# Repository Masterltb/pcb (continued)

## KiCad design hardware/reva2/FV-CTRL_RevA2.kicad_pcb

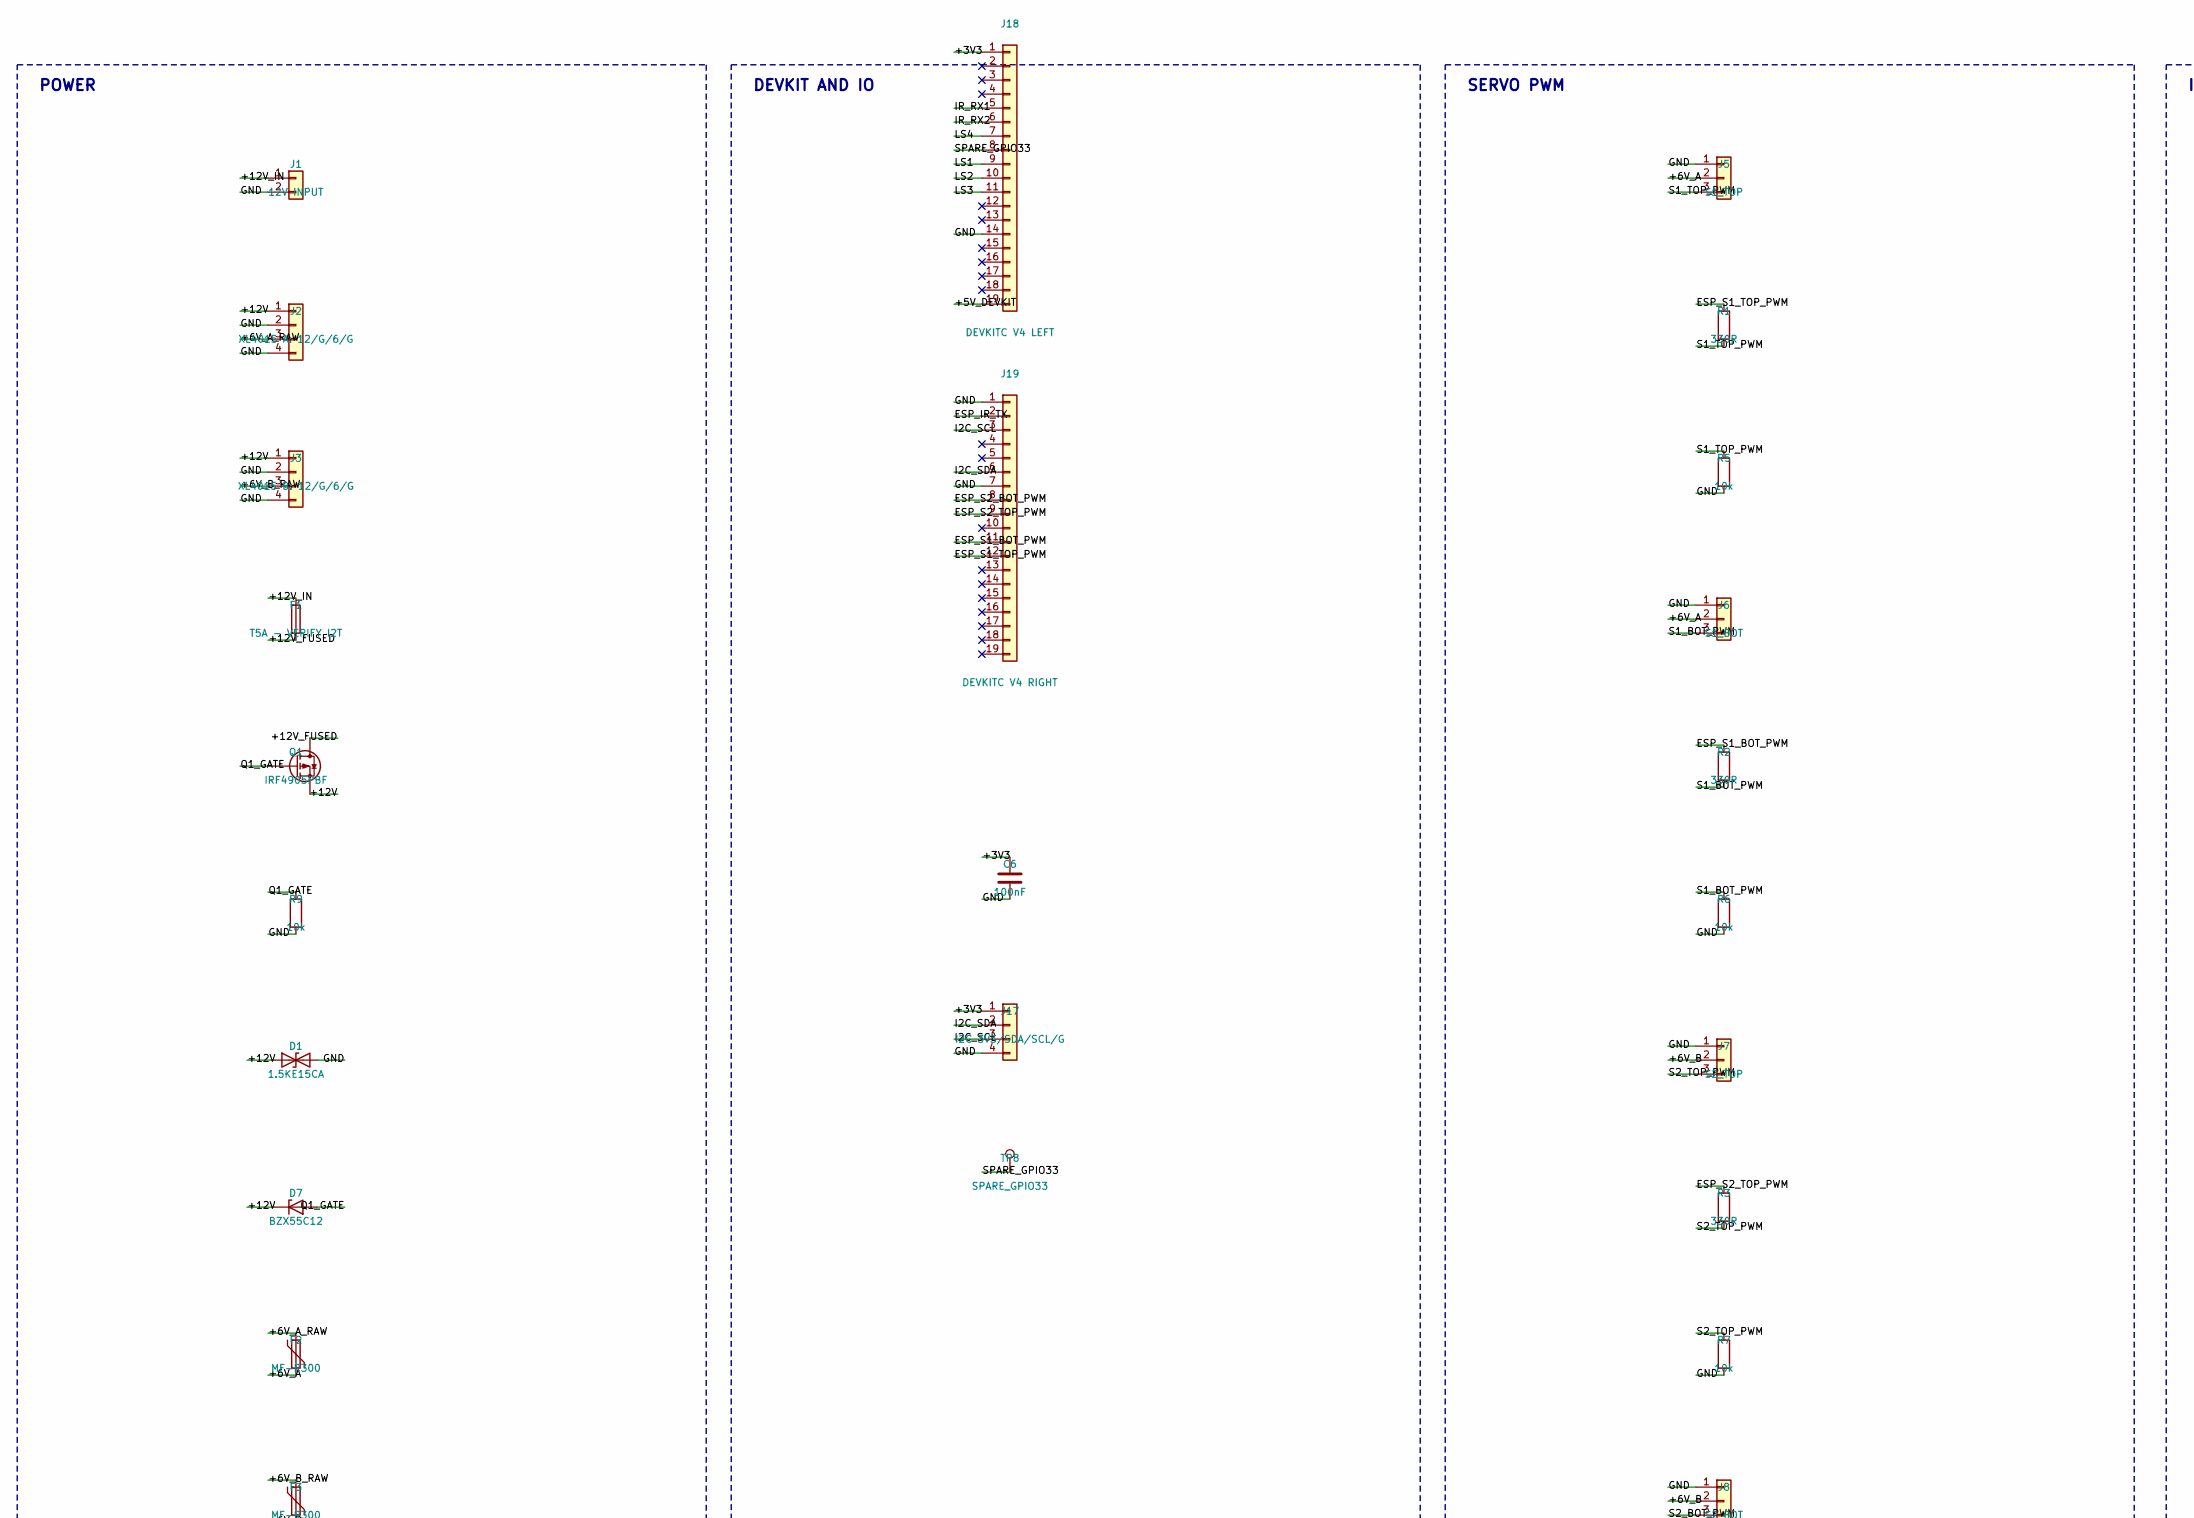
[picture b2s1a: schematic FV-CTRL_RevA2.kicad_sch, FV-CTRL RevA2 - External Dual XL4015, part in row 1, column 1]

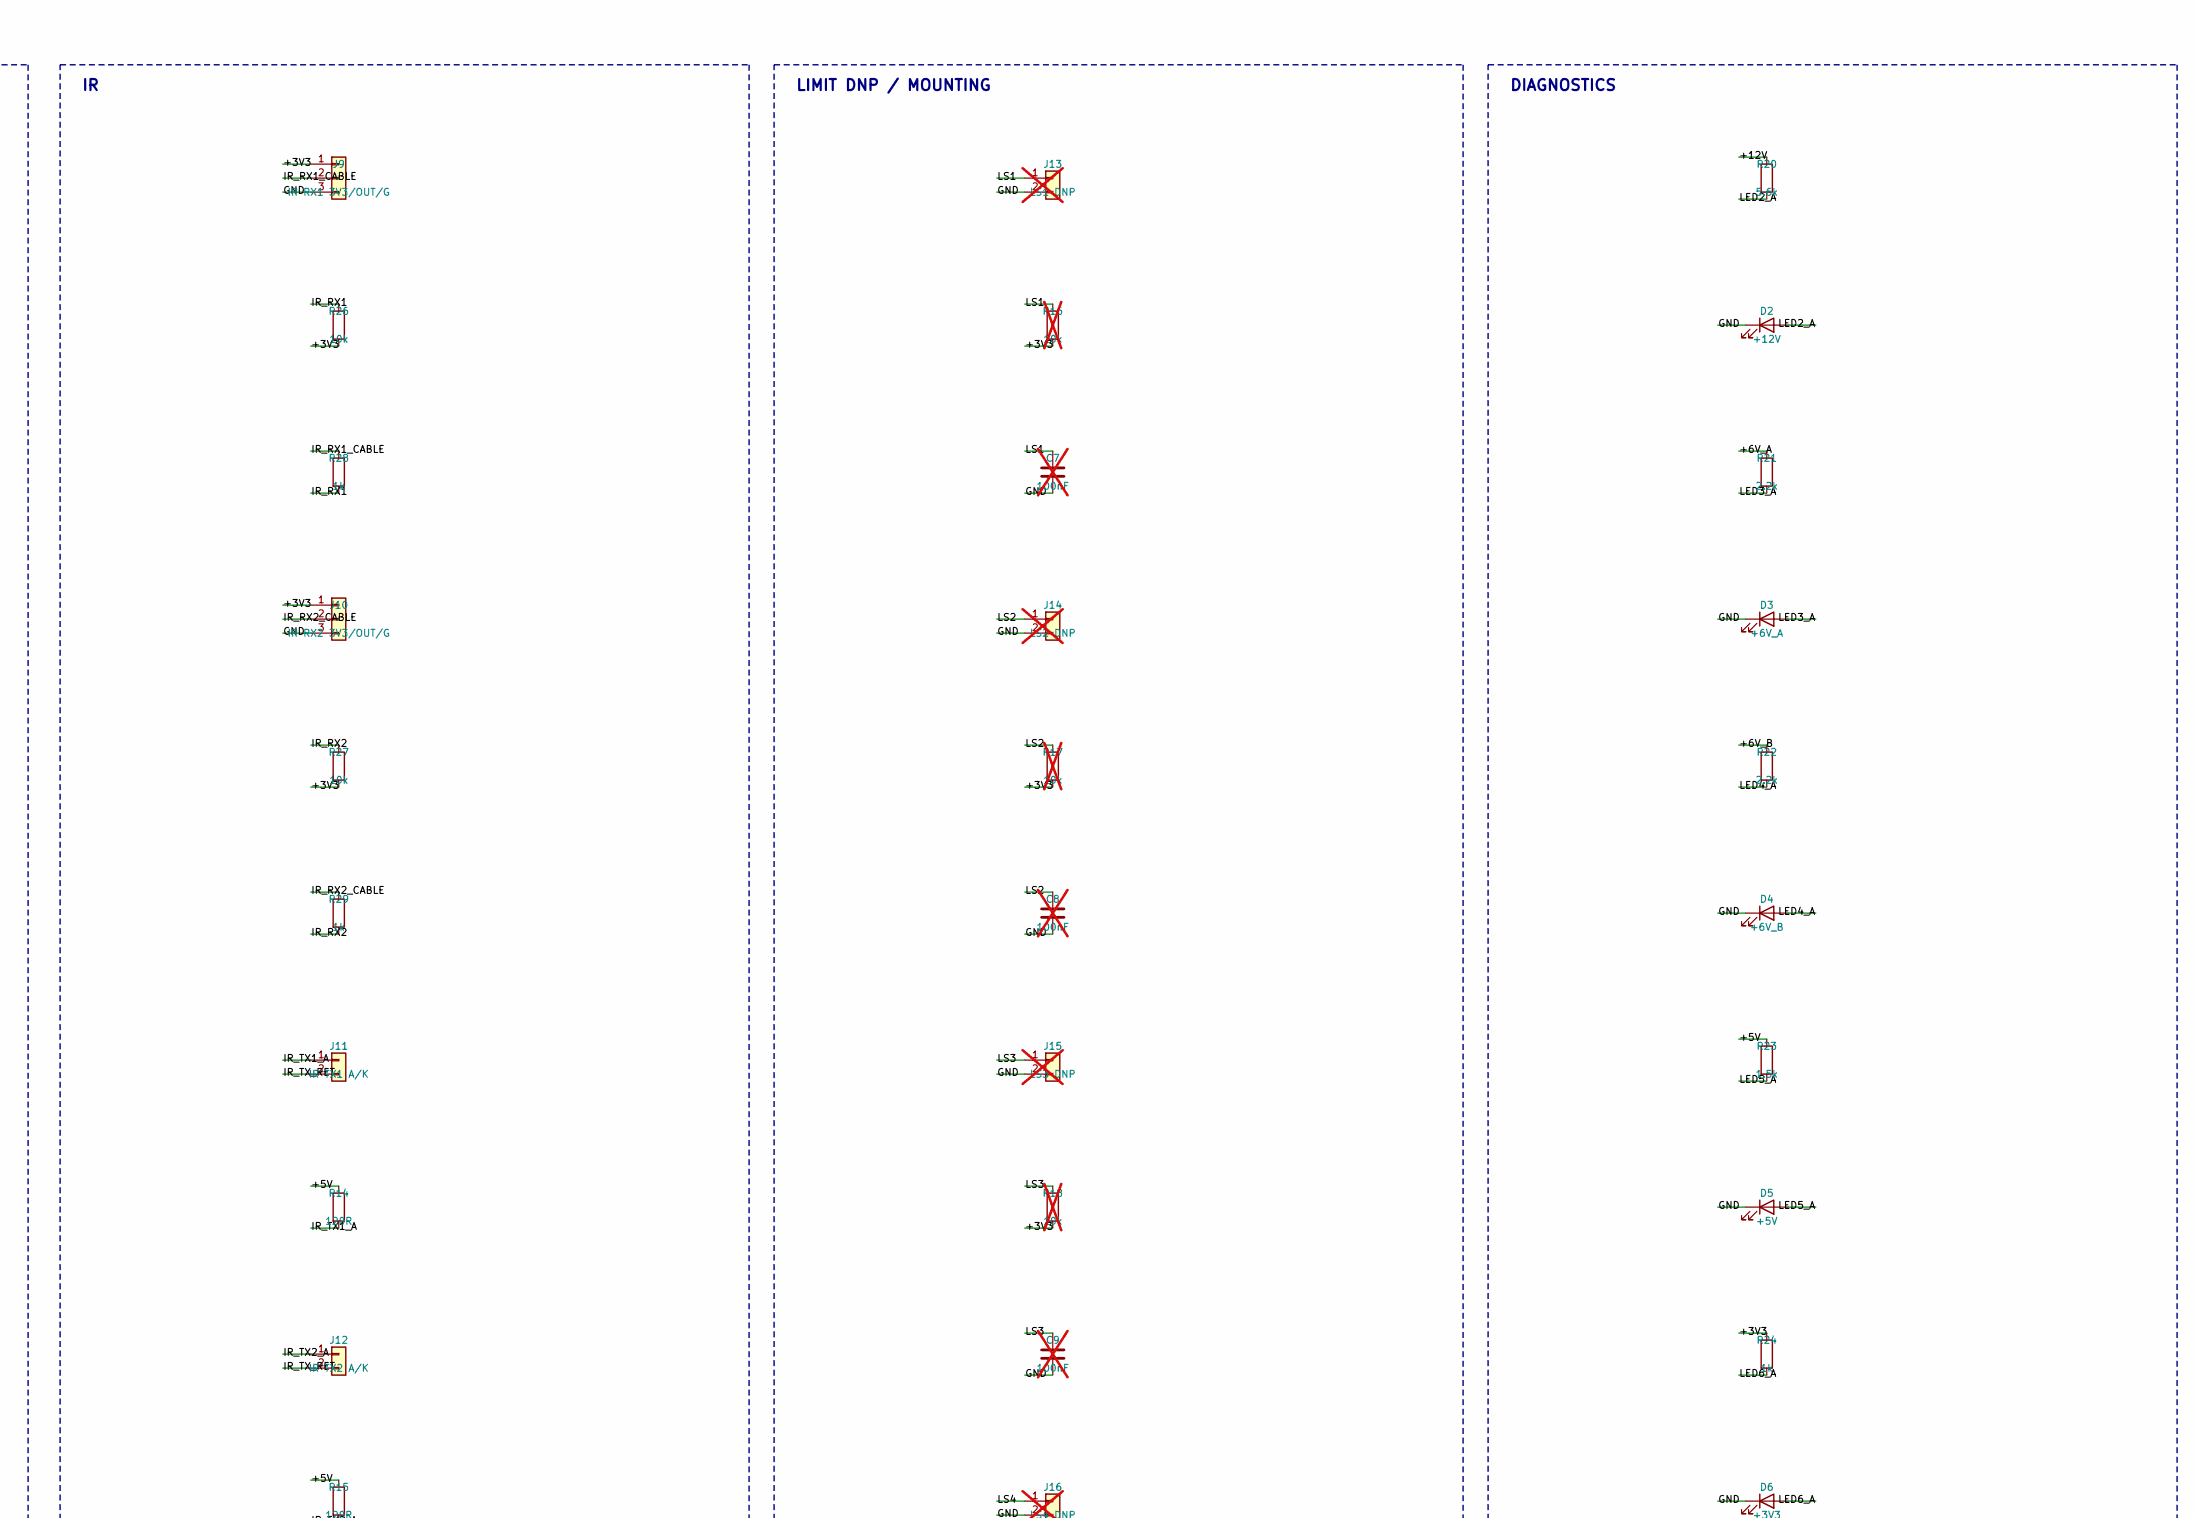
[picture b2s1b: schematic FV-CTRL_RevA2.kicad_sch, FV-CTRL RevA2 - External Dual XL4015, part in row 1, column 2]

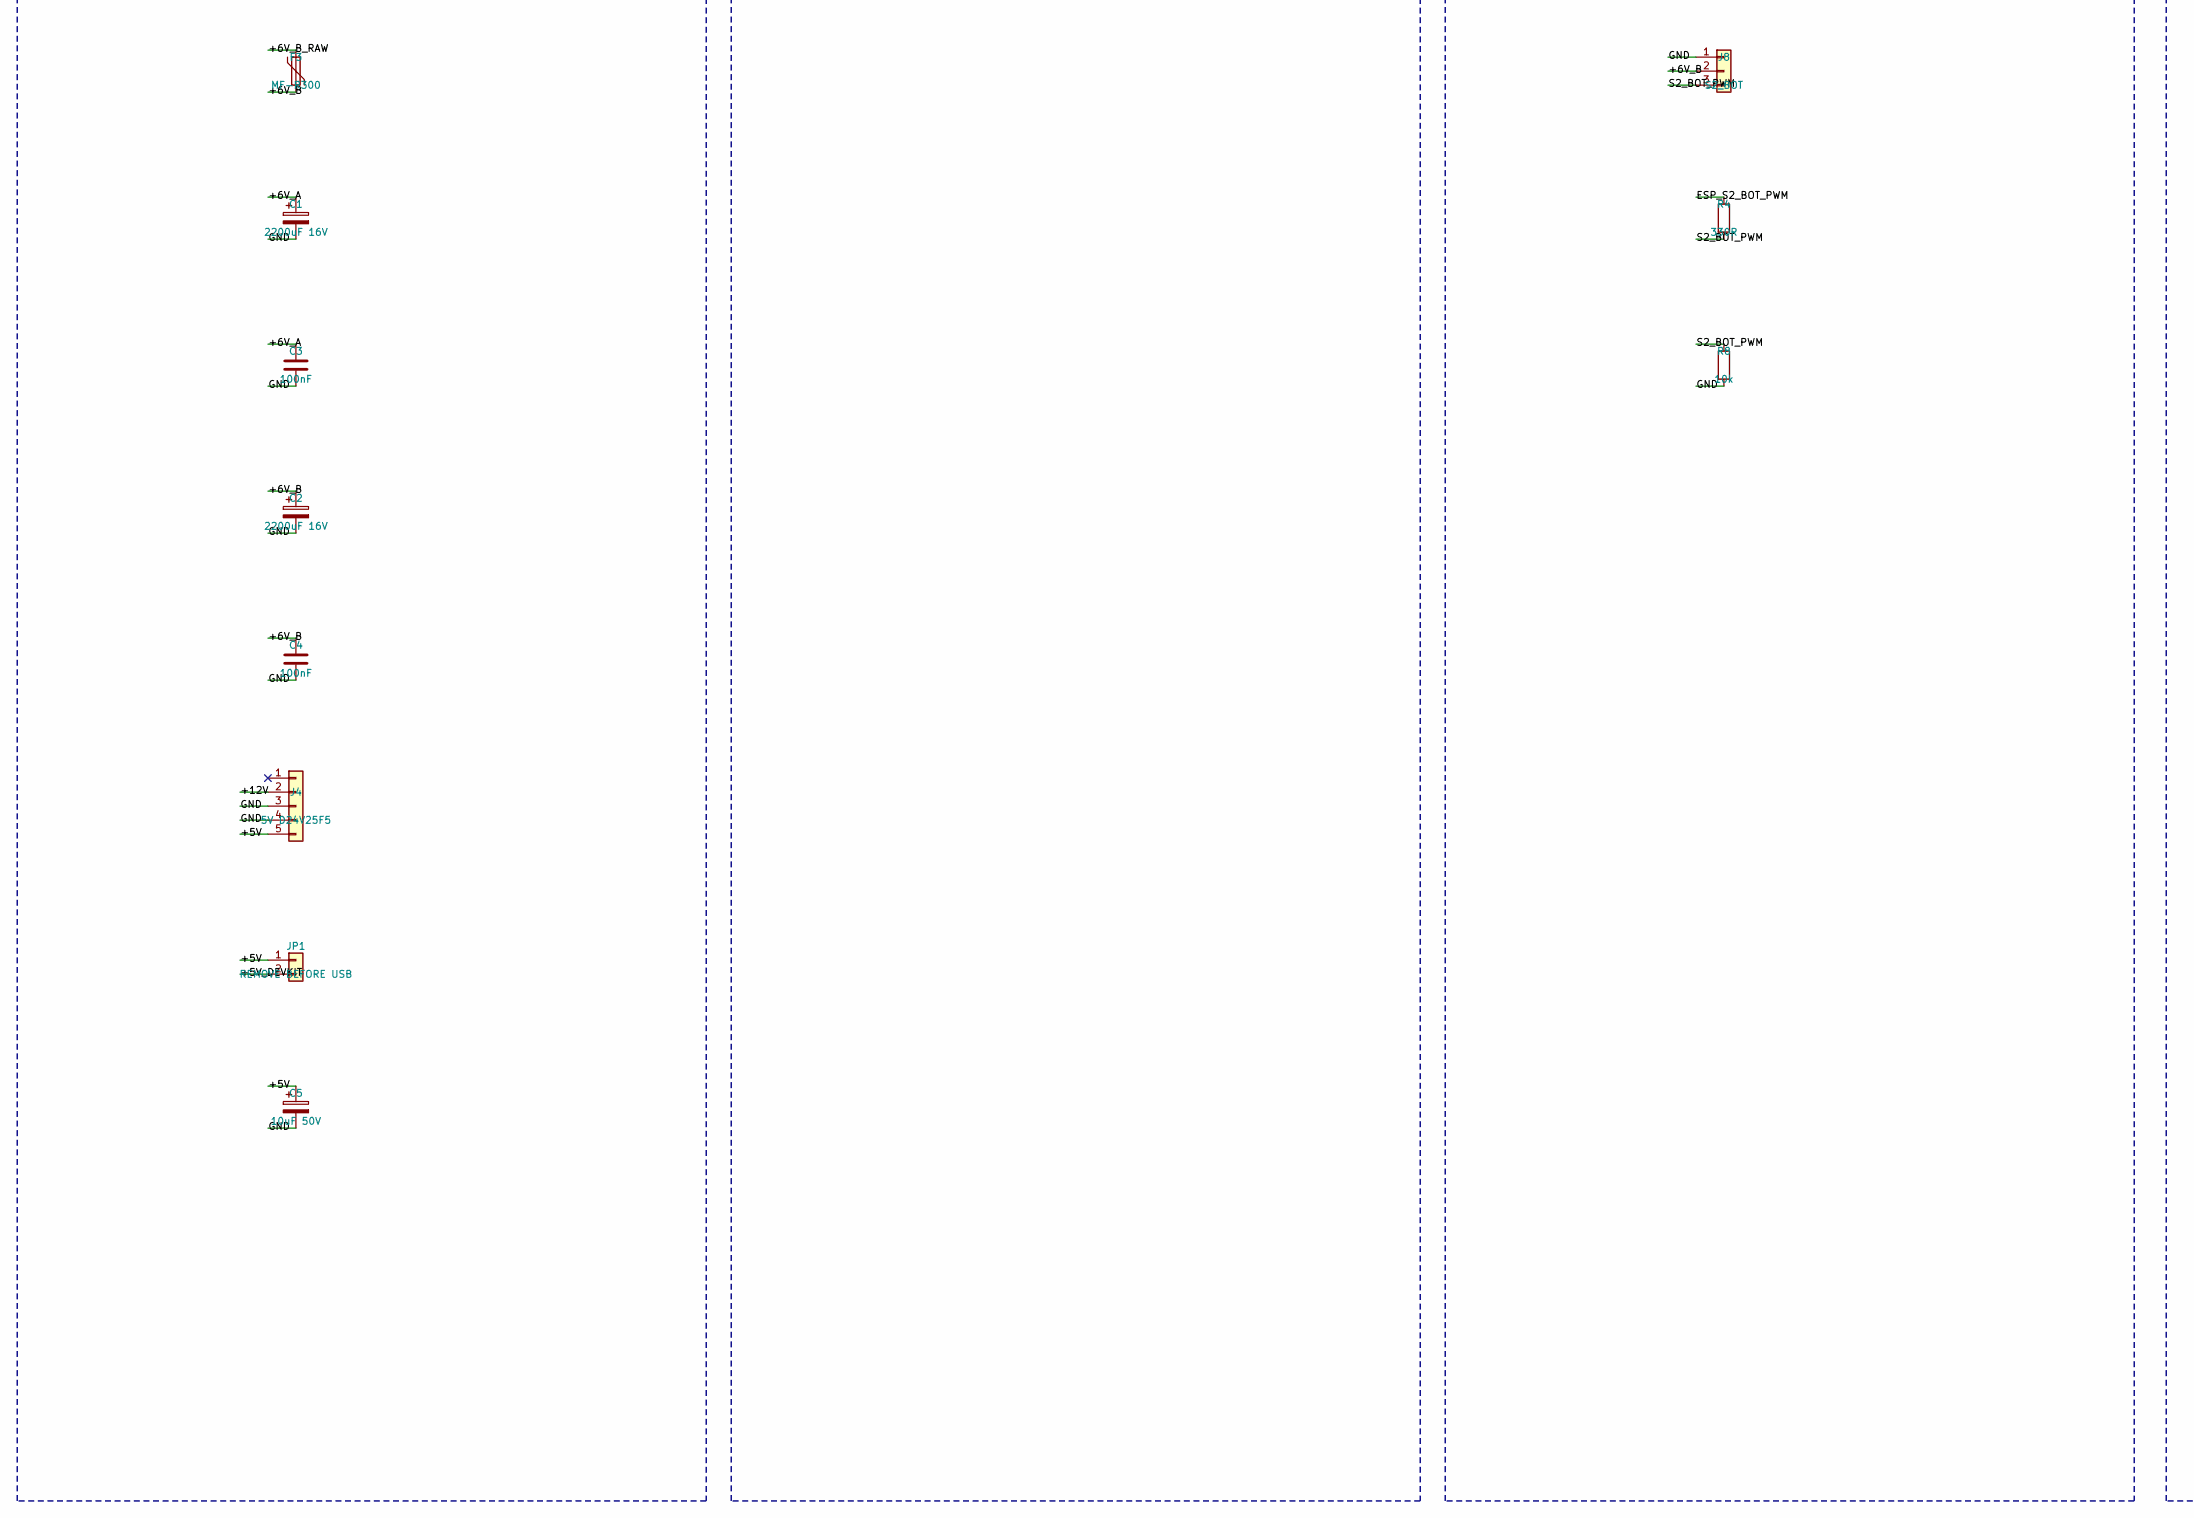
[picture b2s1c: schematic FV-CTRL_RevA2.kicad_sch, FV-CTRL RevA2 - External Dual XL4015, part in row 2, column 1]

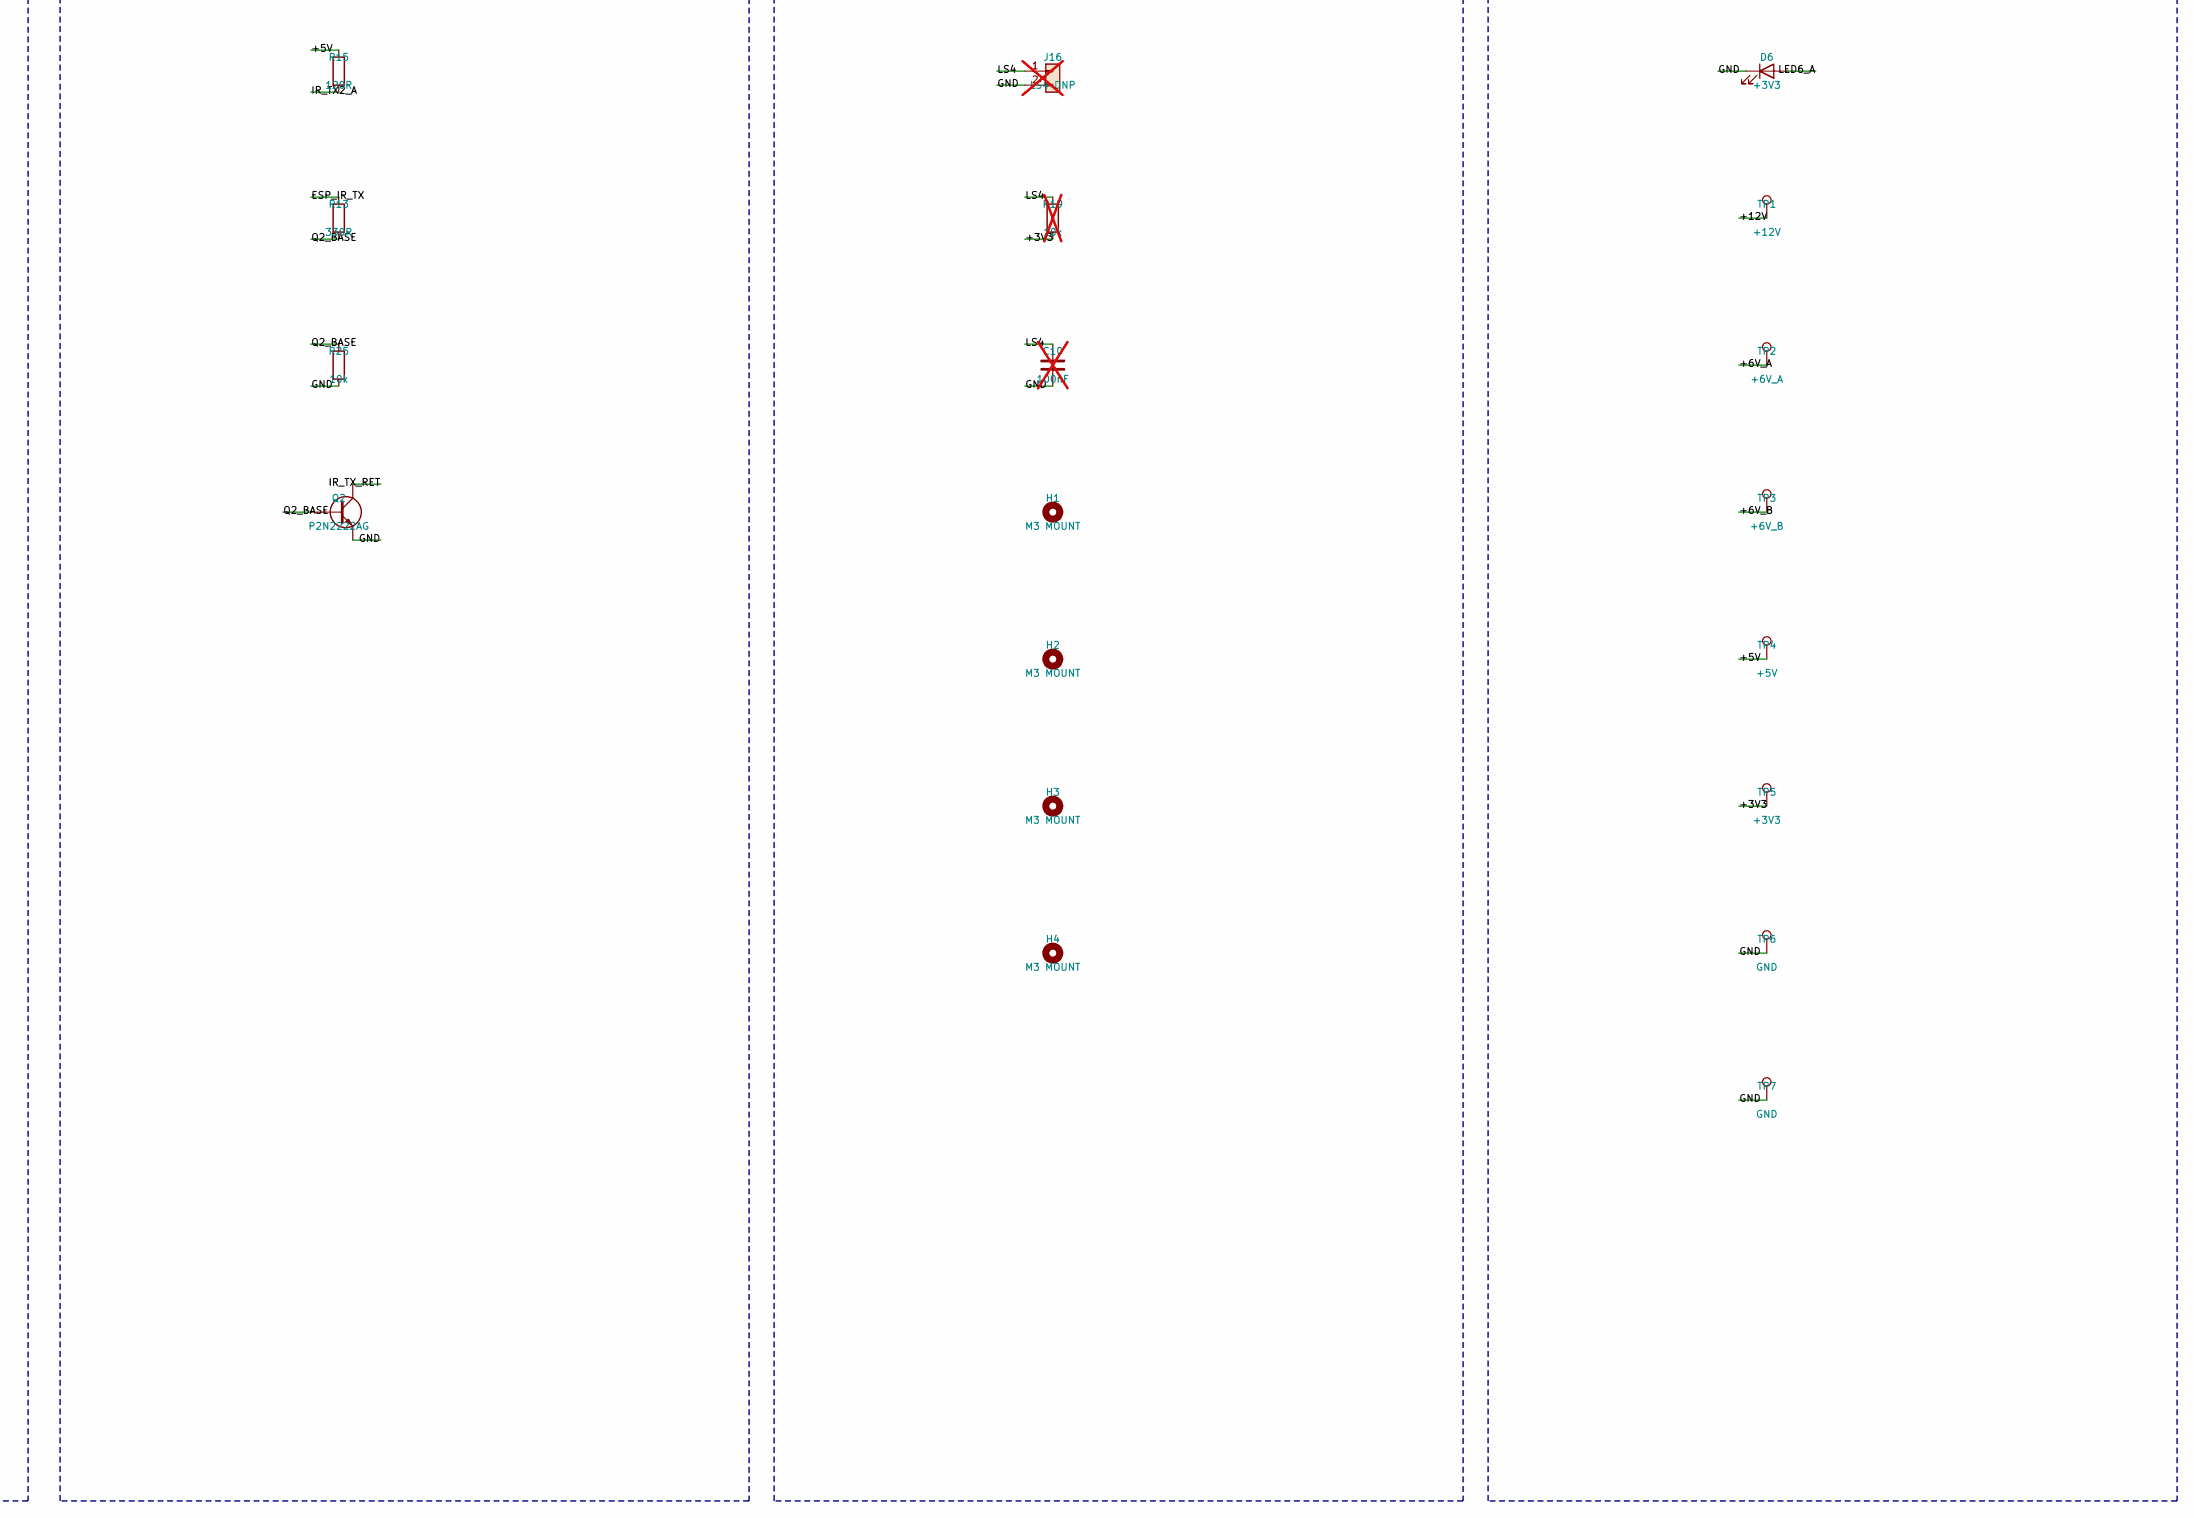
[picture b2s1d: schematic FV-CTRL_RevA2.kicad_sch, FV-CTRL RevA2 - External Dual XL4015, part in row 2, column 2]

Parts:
C1, C2: 2200uF 16V; CP_Radial_D12.5mm_P5.00mm
C3, C4, C6: 100nF; C_Disc_D5.0mm_W2.5mm_P5.00mm
C5: 10uF 50V; CP_Radial_D5.0mm_P2.00mm
C7, C8, C9, C10: 100nF; C_Disc_D5.0mm_W2.5mm_P5.00mm; not fitted
D1: 1.5KE15CA; D_DO-201AD_P15.24mm_Horizontal
D2: +12V; LED_D3.0mm
D3: +6V_A; LED_D3.0mm
D4: +6V_B; LED_D3.0mm
D5: +5V; LED_D3.0mm
D6: +3V3; LED_D3.0mm
D7: BZX55C12; D_DO-35_SOD27_P7.62mm_Horizontal
F1: T5A - VERIFY I2T; Fuseholder_Clip-5x20mm_Littelfuse_111_Inline_P20.00x5.00mm_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
F2, F3: MF-R300; MF_R300
H1, H2, H3, H4: M3 MOUNT; MountingHole_3.2mm_M3
J1: 12V INPUT; PhoenixContact_MSTBA_2,5_2-G-5,08_1x02_P5.08mm_Horizontal
J2: XL4015 A: 12/G/6/G; PhoenixContact_MSTBA_2,5_4-G-5,08_1x04_P5.08mm_Horizontal
J3: XL4015 B: 12/G/6/G; PhoenixContact_MSTBA_2,5_4-G-5,08_1x04_P5.08mm_Horizontal
J4: 5V D24V25F5; Pololu_D24V25F5
J5: S1_TOP; PinHeader_1x03_P2.54mm_Vertical
J6: S1_BOT; PinHeader_1x03_P2.54mm_Vertical
J7: S2_TOP; PinHeader_1x03_P2.54mm_Vertical
J8: S2_BOT; PinHeader_1x03_P2.54mm_Vertical
J9: IR RX1 3V3/OUT/G; JST_XH_B3B-XH-A_1x03_P2.50mm_Vertical
J10: IR RX2 3V3/OUT/G; JST_XH_B3B-XH-A_1x03_P2.50mm_Vertical
J11: IR TX1 A/K; JST_XH_B2B-XH-A_1x02_P2.50mm_Vertical
J12: IR TX2 A/K; JST_XH_B2B-XH-A_1x02_P2.50mm_Vertical
J13: LS1 DNP; JST_XH_B2B-XH-A_1x02_P2.50mm_Vertical; not fitted
J14: LS2 DNP; JST_XH_B2B-XH-A_1x02_P2.50mm_Vertical; not fitted
J15: LS3 DNP; JST_XH_B2B-XH-A_1x02_P2.50mm_Vertical; not fitted
J16: LS4 DNP; JST_XH_B2B-XH-A_1x02_P2.50mm_Vertical; not fitted
J17: I2C 3V3/SDA/SCL/G; PinHeader_1x04_P2.54mm_Vertical
J18: DEVKITC V4 LEFT; PinSocket_1x19_P2.54mm_Vertical
J19: DEVKITC V4 RIGHT; PinSocket_1x19_P2.54mm_Vertical
JP1: REMOVE BEFORE USB; PinHeader_1x02_P2.54mm_Vertical
Q1: IRF4905PBF; PMOS_GDS
Q2: P2N2222AG; NPN_CBE
R1, R2, R3, R4, R13: 330R; R_Axial_DIN0207_L6.3mm_D2.5mm_P7.62mm_Horizontal
R5, R6, R7, R8, R9, R25, R26, R27: 10k; R_Axial_DIN0207_L6.3mm_D2.5mm_P7.62mm_Horizontal
R14, R15: 120R; R_Axial_DIN0207_L6.3mm_D2.5mm_P7.62mm_Horizontal
R16, R17, R18, R19: 10k; R_Axial_DIN0207_L6.3mm_D2.5mm_P7.62mm_Horizontal; not fitted
R20: 5.6k; R_Axial_DIN0207_L6.3mm_D2.5mm_P7.62mm_Horizontal
R21, R22: 2.2k; R_Axial_DIN0207_L6.3mm_D2.5mm_P7.62mm_Horizontal
R23: 1.5k; R_Axial_DIN0207_L6.3mm_D2.5mm_P7.62mm_Horizontal
R24, R28, R29: 1k; R_Axial_DIN0207_L6.3mm_D2.5mm_P7.62mm_Horizontal
TP1: +12V; Keystone_5000_Carrier_D3
TP2: +6V_A; Keystone_5000_Carrier_D3
TP3: +6V_B; Keystone_5000_Carrier_D3
TP4: +5V; Keystone_5000_Carrier_D3
TP5: +3V3; Keystone_5000_Carrier_D3
TP6, TP7: GND; Keystone_5000_Carrier_D3
TP8: SPARE_GPIO33; Keystone_5000_Carrier_D3

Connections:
/+3V3: C6.1, J9.1, J10.1, J17.1, J18.1, R16.2, R17.2, R18.2, R19.2, R24.1, R26.2, R27.2, TP5.1
/+5V: C5.1, J4.5, JP1.1, R14.1, R15.1, R23.1, TP4.1
/+5V_DEVKIT: J18.19, JP1.2
/+6V_A: C1.1, C3.1, F2.2, J5.2, J6.2, R21.1, TP2.1
/+6V_A_RAW: F2.1, J2.3
/+6V_B: C2.1, C4.1, F3.2, J7.2, J8.2, R22.1, TP3.1
/+6V_B_RAW: F3.1, J3.3
/+12V: D1.1 (A1), D7.1 (K), J2.1, J3.1, J4.2, Q1.S, R20.1, TP1.1
/+12V_FUSED: F1.2, Q1.D
/+12V_IN: F1.1, J1.1
/ESP_IR_TX: J19.2, R13.1
/ESP_S1_BOT_PWM: J19.11, R2.1
/ESP_S1_TOP_PWM: J19.12, R1.1
/ESP_S2_BOT_PWM: J19.8, R4.1
/ESP_S2_TOP_PWM: J19.9, R3.1
/GND: C1.2, C2.2, C3.2, C4.2, C5.2, C6.2, C7.2, C8.2, C9.2, C10.2, D1.2 (A2), D2.1 (K), D3.1 (K), D4.1 (K), D5.1 (K), D6.1 (K), J1.2, J2.2, J2.4, J3.2, J3.4, J4.3, J4.4, J5.1, J6.1, J7.1, J8.1, J9.3, J10.3, J13.2, J14.2, J15.2, J16.2, J17.4, J18.14, J19.1, J19.7, Q2.E, R5.2, R6.2, R7.2, R8.2, R9.2, R25.2, TP6.1, TP7.1
/I2C_SCL: J17.3, J19.3
/I2C_SDA: J17.2, J19.6
/IR_RX1: J18.5, R26.1, R28.2
/IR_RX1_CABLE: J9.2, R28.1
/IR_RX2: J18.6, R27.1, R29.2
/IR_RX2_CABLE: J10.2, R29.1
/IR_TX1_A: J11.1, R14.2
/IR_TX2_A: J12.1, R15.2
/IR_TX_RET: J11.2, J12.2, Q2.C
/LED2_A: D2.2 (A), R20.2
/LED3_A: D3.2 (A), R21.2
/LED4_A: D4.2 (A), R22.2
/LED5_A: D5.2 (A), R23.2
/LED6_A: D6.2 (A), R24.2
/LS1: C7.1, J13.1, J18.9, R16.1
/LS2: C8.1, J14.1, J18.10, R17.1
/LS3: C9.1, J15.1, J18.11, R18.1
/LS4: C10.1, J16.1, J18.7, R19.1
/Q1_GATE: D7.2 (A), Q1.G, R9.1
/Q2_BASE: Q2.B, R13.2, R25.1
/S1_BOT_PWM: J6.3, R2.2, R6.1
/S1_TOP_PWM: J5.3, R1.2, R5.1
/S2_BOT_PWM: J8.3, R4.2, R8.1
/S2_TOP_PWM: J7.3, R3.2, R7.1
/SPARE_GPIO33: J18.8, TP8.1

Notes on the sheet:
POWER
DEVKIT AND IO
SERVO PWM
LIMIT DNP / MOUNTING
DIAGNOSTICS

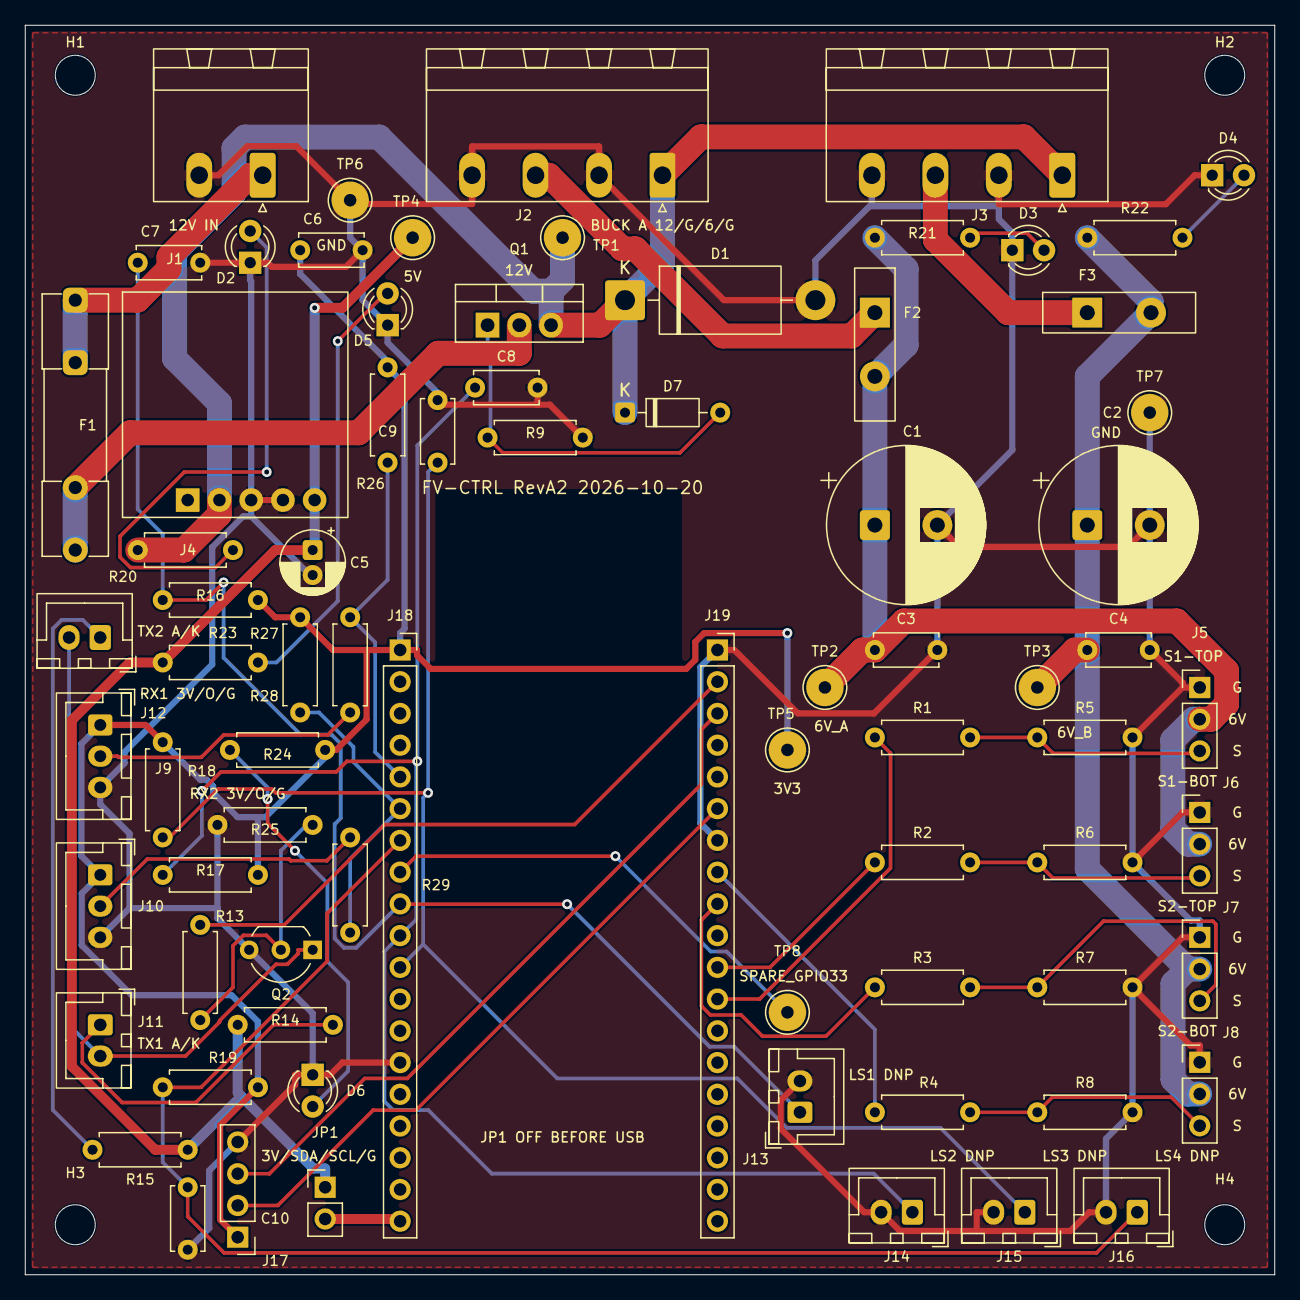
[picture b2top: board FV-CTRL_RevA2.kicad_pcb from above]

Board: 2 copper layers, 100.0 x 100.0 mm, 80 parts (0 on the bottom side), 41 nets.

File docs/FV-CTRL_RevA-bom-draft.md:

# BOM Nháp FV-CTRL Rev A (Engineering Draft)

| Ref | Giá trị / Mô tả | Thư viện | Footprint | DNP | MPN / Ghi chú |
|---|---|---|---|---|---|
| J1 | 12V_IN | `Connector_Generic:Conn_01x02` | TerminalBlock_Phoenix:TerminalBlock_Phoenix_MKDS-1,5-2-5.08_1x02_P5.08mm_Horizontal | No | Pluggable 2-pin 5.0mm |
| F1 | 5A 250V | `Device:Fuse` | Fuse:Fuseholder_Clip-5x20mm_Littelfuse_111_Inline_P20.00x5.00mm_D1.05mm_Horizontal | No | 5x20mm 5A cartridge |
| Q1 | IRF9540N | `Device:Q_PMOS` | Package_TO_SOT_THT:TO-220-3_Vertical | No | IRF9540NPBF |
| R9 | 10k | `Device:R` | Resistor_THT:R_Axial_DIN0207_L6.3mm_D2.5mm_P7.62mm_Horizontal | No | 10k 1/4W 5% |
| D1 | 1.5KE15CA | `Device:D_TVS` | Diode_THT:D_DO-201_P12.70mm_Horizontal | No | 1.5KE15CA |
| J2 | XH-M401 (6.0V 8A) | `Connector_Generic:Conn_01x04` | fv_modules:Converter_DCDC_XH-M401_8A | No | XH-M401 (XL4016E1 8A 200W) |
| J3 | AUX_BUCK (DNP) | `Connector_Generic:Conn_01x04` | Connector_PinHeader_2.54mm:PinHeader_1x04_P2.54mm_Vertical | DNP | Auxiliary 4-pin Header |
| J4 | MP1584EN (5V Logic) | `Connector_Generic:Conn_01x04` | fv_modules:Converter_DCDC_MP1584EN | No | MP1584EN Mini 3A Buck |
| F2 | PTC 3A | `Device:Polyfuse` | Fuse:Fuse_Bourns_MF-RG300 | No | Bourns MF-R300 |
| C1 | 1000-2200uF 16V | `Device:C_Polarized` | Capacitor_THT:CP_Radial_D12.5mm_P5.00mm | No | 1000uF 16V Radial |
| C3 | 100nF | `Device:C` | Capacitor_THT:C_Disc_D5.0mm_W2.5mm_P5.00mm | No | 100nF 50V Ceramic |
| J5 | S1_TOP | `Connector_Generic:Conn_01x03` | Connector_PinHeader_2.54mm:PinHeader_1x03_P2.54mm_Vertical | No | 3-pin Header |
| J6 | S1_BOT | `Connector_Generic:Conn_01x03` | Connector_PinHeader_2.54mm:PinHeader_1x03_P2.54mm_Vertical | No | 3-pin Header |
| F3 | PTC 3A | `Device:Polyfuse` | Fuse:Fuse_Bourns_MF-RG300 | No | Bourns MF-R300 |
| C2 | 1000-2200uF 16V | `Device:C_Polarized` | Capacitor_THT:CP_Radial_D12.5mm_P5.00mm | No | 1000uF 16V Radial |
| C4 | 100nF | `Device:C` | Capacitor_THT:C_Disc_D5.0mm_W2.5mm_P5.00mm | No | 100nF 50V Ceramic |
| J7 | S2_TOP | `Connector_Generic:Conn_01x03` | Connector_PinHeader_2.54mm:PinHeader_1x03_P2.54mm_Vertical | No | 3-pin Header |
| J8 | S2_BOT | `Connector_Generic:Conn_01x03` | Connector_PinHeader_2.54mm:PinHeader_1x03_P2.54mm_Vertical | No | 3-pin Header |
| J18 | ESP32_Left (Pins 1-19) | `Connector_Generic:Conn_01x19` | Connector_PinSocket_2.54mm:PinSocket_1x19_P2.54mm_Vertical | No | 19-pin Female Header 2.54mm |
| J19 | ESP32_Right (Pins 20-38) | `Connector_Generic:Conn_01x19` | Connector_PinSocket_2.54mm:PinSocket_1x19_P2.54mm_Vertical | No | 19-pin Female Header 2.54mm |
| R1 | 330R | `Device:R` | Resistor_THT:R_Axial_DIN0207_L6.3mm_D2.5mm_P7.62mm_Horizontal | No | 330R 1/4W 5% |
| R5 | 10k | `Device:R` | Resistor_THT:R_Axial_DIN0207_L6.3mm_D2.5mm_P7.62mm_Horizontal | No | 10k 1/4W 5% |
| R2 | 330R | `Device:R` | Resistor_THT:R_Axial_DIN0207_L6.3mm_D2.5mm_P7.62mm_Horizontal | No | 330R 1/4W 5% |
| R6 | 10k | `Device:R` | Resistor_THT:R_Axial_DIN0207_L6.3mm_D2.5mm_P7.62mm_Horizontal | No | 10k 1/4W 5% |
| R3 | 330R | `Device:R` | Resistor_THT:R_Axial_DIN0207_L6.3mm_D2.5mm_P7.62mm_Horizontal | No | 330R 1/4W 5% |
| R7 | 10k | `Device:R` | Resistor_THT:R_Axial_DIN0207_L6.3mm_D2.5mm_P7.62mm_Horizontal | No | 10k 1/4W 5% |
| R4 | 330R | `Device:R` | Resistor_THT:R_Axial_DIN0207_L6.3mm_D2.5mm_P7.62mm_Horizontal | No | 330R 1/4W 5% |
| R8 | 10k | `Device:R` | Resistor_THT:R_Axial_DIN0207_L6.3mm_D2.5mm_P7.62mm_Horizontal | No | 10k 1/4W 5% |
| R13 | 1k | `Device:R` | Resistor_THT:R_Axial_DIN0207_L6.3mm_D2.5mm_P7.62mm_Horizontal | No | 1k 1/4W 5% |
| Q2 | S8050 | `Device:Q_NPN` | Package_TO_SOT_THT:TO-92_Inline | No | S8050 |
| R14 | 120R | `Device:R` | Resistor_THT:R_Axial_DIN0207_L6.3mm_D2.5mm_P7.62mm_Horizontal | No | 120R 1/2W 5% |
| J11 | IR_TX1 (Col 1) | `Connector_Generic:Conn_01x02` | Connector_JST:JST_XH_B2B-XH-A_1x02_P2.50mm_Vertical | No | JST-XH 2-pin |
| R15 | 120R | `Device:R` | Resistor_THT:R_Axial_DIN0207_L6.3mm_D2.5mm_P7.62mm_Horizontal | No | 120R 1/2W 5% |
| J12 | IR_TX2 (Col 2) | `Connector_Generic:Conn_01x02` | Connector_JST:JST_XH_B2B-XH-A_1x02_P2.50mm_Vertical | No | JST-XH 2-pin |
| J9 | IR_RX1 | `Connector_Generic:Conn_01x03` | Connector_JST:JST_XH_B3B-XH-A_1x03_P2.50mm_Vertical | No | JST-XH 3-pin |
| J10 | IR_RX2 | `Connector_Generic:Conn_01x03` | Connector_JST:JST_XH_B3B-XH-A_1x03_P2.50mm_Vertical | No | JST-XH 3-pin |
| J13 | LS1 (DNP) | `Connector_Generic:Conn_01x02` | Connector_JST:JST_XH_B2B-XH-A_1x02_P2.50mm_Vertical | DNP | JST-XH 2-pin |
| R16 | 10k (DNP) | `Device:R` | Resistor_THT:R_Axial_DIN0207_L6.3mm_D2.5mm_P7.62mm_Horizontal | DNP | 10k 1/4W 5% |
| C7 | 100nF (DNP) | `Device:C` | Capacitor_THT:C_Disc_D5.0mm_W2.5mm_P5.00mm | DNP | 100nF 50V Ceramic |
| J14 | LS2 (DNP) | `Connector_Generic:Conn_01x02` | Connector_JST:JST_XH_B2B-XH-A_1x02_P2.50mm_Vertical | DNP | JST-XH 2-pin |
| R17 | 10k (DNP) | `Device:R` | Resistor_THT:R_Axial_DIN0207_L6.3mm_D2.5mm_P7.62mm_Horizontal | DNP | 10k 1/4W 5% |
| C8 | 100nF (DNP) | `Device:C` | Capacitor_THT:C_Disc_D5.0mm_W2.5mm_P5.00mm | DNP | 100nF 50V Ceramic |
| J15 | LS3 (DNP) | `Connector_Generic:Conn_01x02` | Connector_JST:JST_XH_B2B-XH-A_1x02_P2.50mm_Vertical | DNP | JST-XH 2-pin |
| R18 | 10k (DNP) | `Device:R` | Resistor_THT:R_Axial_DIN0207_L6.3mm_D2.5mm_P7.62mm_Horizontal | DNP | 10k 1/4W 5% |
| C9 | 100nF (DNP) | `Device:C` | Capacitor_THT:C_Disc_D5.0mm_W2.5mm_P5.00mm | DNP | 100nF 50V Ceramic |
| J16 | LS4 (DNP) | `Connector_Generic:Conn_01x02` | Connector_JST:JST_XH_B2B-XH-A_1x02_P2.50mm_Vertical | DNP | JST-XH 2-pin |
| R19 | 10k (DNP) | `Device:R` | Resistor_THT:R_Axial_DIN0207_L6.3mm_D2.5mm_P7.62mm_Horizontal | DNP | 10k 1/4W 5% |
| C10 | 100nF (DNP) | `Device:C` | Capacitor_THT:C_Disc_D5.0mm_W2.5mm_P5.00mm | DNP | 100nF 50V Ceramic |
| C5 | 10uF 16V | `Device:C_Polarized` | Capacitor_THT:C_Disc_D5.0mm_W2.5mm_P5.00mm | No | 10uF 16V Radial |
| C6 | 100nF | `Device:C` | Capacitor_THT:C_Disc_D5.0mm_W2.5mm_P5.00mm | No | 100nF 50V Ceramic |
| R20 | 5.6k | `Device:R` | Resistor_THT:R_Axial_DIN0207_L6.3mm_D2.5mm_P7.62mm_Horizontal | No | 5.6k 1/4W 5% |
| D2 | LED_+12V | `Device:LED` | LED_THT:LED_D3.0mm | No | 3mm Green LED |
| R21 | 2.2k | `Device:R` | Resistor_THT:R_Axial_DIN0207_L6.3mm_D2.5mm_P7.62mm_Horizontal | No | 2.2k 1/4W 5% |
| D3 | LED_+6V_A | `Device:LED` | LED_THT:LED_D3.0mm | No | 3mm Green LED |
| R22 | 2.2k | `Device:R` | Resistor_THT:R_Axial_DIN0207_L6.3mm_D2.5mm_P7.62mm_Horizontal | No | 2.2k 1/4W 5% |
| D4 | LED_+6V_B | `Device:LED` | LED_THT:LED_D3.0mm | No | 3mm Green LED |
| R23 | 1.5k | `Device:R` | Resistor_THT:R_Axial_DIN0207_L6.3mm_D2.5mm_P7.62mm_Horizontal | No | 1.5k 1/4W 5% |
| D5 | LED_+5V | `Device:LED` | LED_THT:LED_D3.0mm | No | 3mm Green LED |
| R24 | 1.0k | `Device:R` | Resistor_THT:R_Axial_DIN0207_L6.3mm_D2.5mm_P7.62mm_Horizontal | No | 1.0k 1/4W 5% |
| D6 | LED_+3V3 | `Device:LED` | LED_THT:LED_D3.0mm | No | 3mm Green LED |
| TP1 | TP_+12V | `Connector:TestPoint` | TestPoint:TestPoint_Pad_D2.0mm | No | Test Point Loop THT |
| TP2 | TP_+6V_A | `Connector:TestPoint` | TestPoint:TestPoint_Pad_D2.0mm | No | Test Point Loop THT |
| TP3 | TP_+6V_B | `Connector:TestPoint` | TestPoint:TestPoint_Pad_D2.0mm | No | Test Point Loop THT |
| TP4 | TP_+5V | `Connector:TestPoint` | TestPoint:TestPoint_Pad_D2.0mm | No | Test Point Loop THT |
| TP5 | TP_+3V3 | `Connector:TestPoint` | TestPoint:TestPoint_Pad_D2.0mm | No | Test Point Loop THT |
| TP6 | TP_GND | `Connector:TestPoint` | TestPoint:TestPoint_Pad_D2.0mm | No | Test Point Loop THT |
| TP7 | TP_GND | `Connector:TestPoint` | TestPoint:TestPoint_Pad_D2.0mm | No | Test Point Loop THT |
| TP8 | TP_SPARE_GPIO33 | `Connector:TestPoint` | TestPoint:TestPoint_Pad_D2.0mm | No | Test Point Loop THT |
| J17 | I2C_RESERVED | `Connector_Generic:Conn_01x04` | Connector_PinHeader_2.54mm:PinHeader_1x04_P2.54mm_Vertical | No | 4-pin Header 2.54mm |

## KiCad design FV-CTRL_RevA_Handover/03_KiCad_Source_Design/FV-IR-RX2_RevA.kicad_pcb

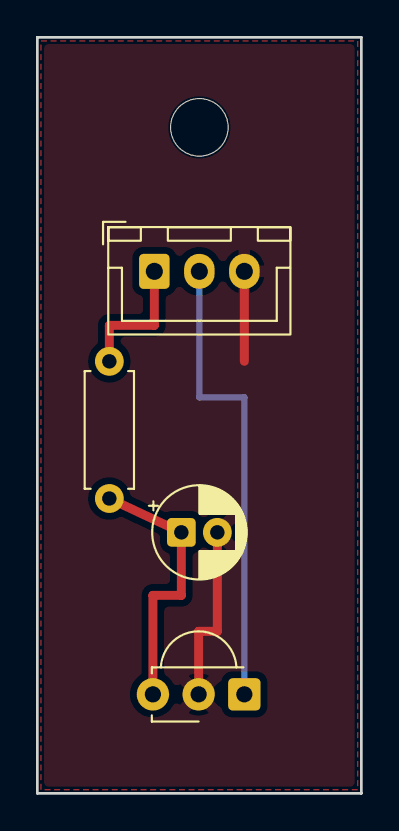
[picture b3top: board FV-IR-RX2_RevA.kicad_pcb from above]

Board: 2 copper layers, 18.0 x 42.0 mm, 5 parts (0 on the bottom side), 4 nets.

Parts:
C1: 4.7uF; CP_Radial_D5.0mm_P2.00mm
H1: MountingHole_3.2mm_M3
J1: JST_XH_3P; JST_XH_B3B-XH-A_1x03_P2.50mm_Vertical
R1: 100R; R_Axial_DIN0207_L6.3mm_D2.5mm_P7.62mm_Horizontal
U1: TSOP38238 / VS1838B; Vishay_MINICAST-3Pin

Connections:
+3V3_FILT: C1.1, R1.2, U1.3
+3V3_IN: J1.1, R1.1
GND: C1.2, J1.3, U1.2
IR_RX_OUT: J1.2, U1.1
